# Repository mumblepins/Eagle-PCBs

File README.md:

# Eagle-PCBs
Various eagle boards.

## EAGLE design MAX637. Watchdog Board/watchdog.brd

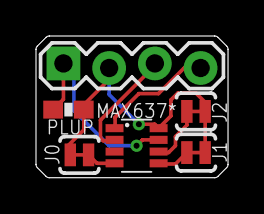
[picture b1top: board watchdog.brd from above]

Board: 2 copper layers, 10.7 x 7.9 mm, 6 parts (0 on the bottom side), 7 nets.

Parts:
JP1: 1X04_LOCK
PLUP: 0603-RES
U$1: MAX6374KA; SOT23-8L
U$2, U$3, U$4: JUMPER-PAD-2-NC_BY_TRACE; PAD-JUMPER-2-NC_BY_TRACE_YES_SILK

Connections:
GND: JP1.3, U$1.2
unnamed: U$1.4, U$2.1
unnamed: U$1.5, U$3.2
unnamed: U$1.6, U$4.2
unnamed: JP1.1, PLUP.1, U$1.7
unnamed: JP1.4, U$1.1
VCC: JP1.2, PLUP.2, U$1.8, U$2.2, U$3.1, U$4.1

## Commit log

2015-02-11 Maxim watchdog breakout board

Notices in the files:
parts and their libraries:
SparkFun-Connectors: Licensing: Creative Commons ShareAlike 4.0 International - https://creativecommons.org/licenses/by-sa/4.0
